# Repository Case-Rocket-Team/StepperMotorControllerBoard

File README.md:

"# StepperDriver" 
"# StepperMotorControllerBoard"

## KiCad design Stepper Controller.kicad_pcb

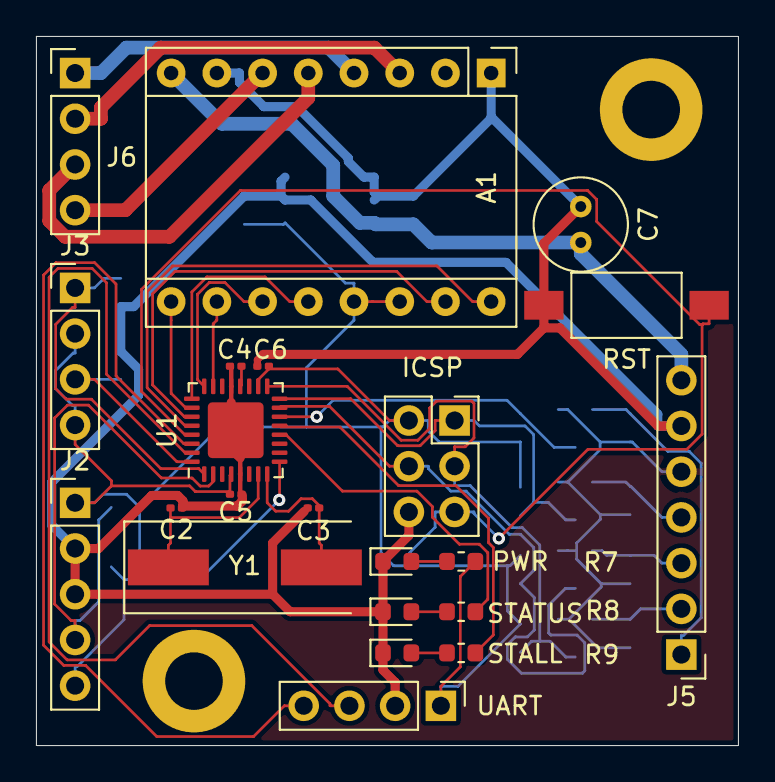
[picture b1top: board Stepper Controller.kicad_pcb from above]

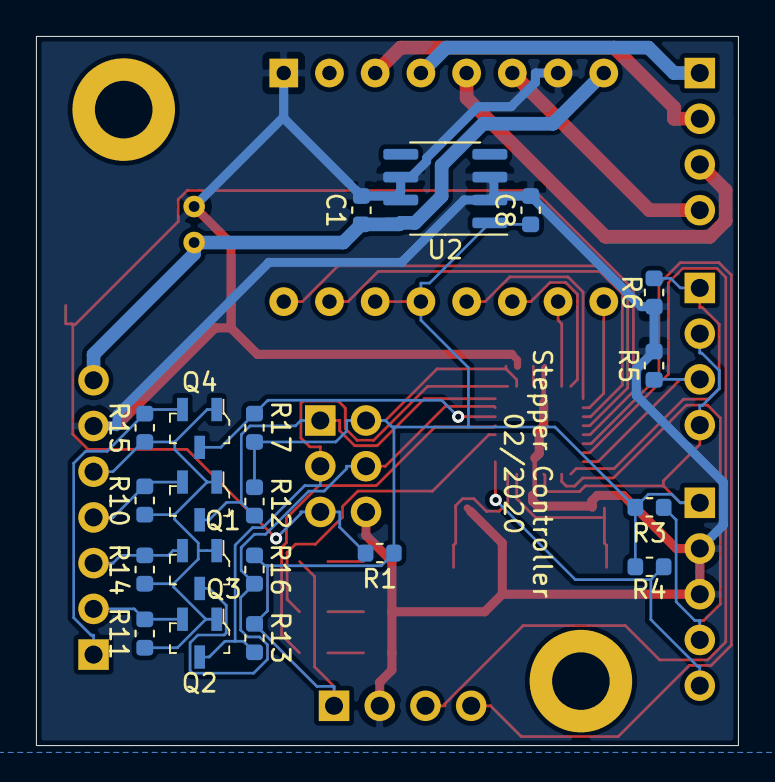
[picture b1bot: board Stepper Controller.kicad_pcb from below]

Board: 2 copper layers, 39.0 x 39.4 mm, 44 parts (20 on the bottom side), 37 nets.

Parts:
A1: Pololu_Breakout_DRV8825; Pololu_Breakout-16_15.2x20.3mm
C1: .33uF; C_0603_1608Metric
C2, C3: 22pf; C_0201_0603Metric
C4, C5, C6: 0.1uF; C_0201_0603Metric
C7: 100uf; C_Radial_D5.0mm_H5.0mm_P2.00mm
C8: .1uF; C_0603_1608Metric
J2: ENCODER; PinHeader_1x05_P2.54mm_Vertical
J3: LIMIT_SWITCH; PinHeader_1x04_P2.54mm_Vertical
J4: ICSP; PinSocket_2x03_P2.54mm_Vertical
J5: MAIN_CONNECTOR; PinHeader_1x07_P2.54mm_Vertical
J6: Stepper; PinHeader_1x04_P2.54mm_Vertical
PWR: PWR; LED_0603_1608Metric
Q1, Q2, Q3, Q4: BSS138; SOT-23-3
R1, R3, R4, R5, R6, R7, R8, R9, R10, R11, R12, R13, R14, R15, R16, R17: 10K; R_0603_1608Metric
REF1, REF2: MountingHole_3.2mm_M3_ISO7380_Pad
RST: RESET; SW_SPST_FSMSM
STALL: STALL; LED_0603_1608Metric
STATUS: STATUS; LED_0603_1608Metric
U1: ATmega328PB-MU; QFN-32-1EP_5x5mm_P0.5mm_EP3.1x3.1mm
U2: L78L05_SO8; SOIC-8_3.9x4.9mm_P1.27mm
UART: UART; PinHeader_1x04_P2.54mm_Vertical
Y1: 16 MHz; Crystal_SMD_HC49-SD

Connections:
+3V3: J5.5, Q1.1, Q2.1, Q3.1, Q4.1, R10.1, R11.1, R14.1, R15.1
+5V: A1.13, A1.14, C5.1, C6.1, C8.1, J2.1, J3.2, J3.4, J4.2, R1.1, R3.2, R4.2, R7.2, R12.1, R13.1, R16.1, R17.1, U1.4, U1.18, U2.1, UART.1
+12V: A1.8, C1.1, C7.2, J5.7, U2.8
CS_3V3: J5.1, Q4.2, R15.2
CS_5V: Q4.3, R17.2, U1.14
DIR: A1.16, U1.28
ENCDR_A: J2.4, R3.1, U1.2
ENCDR_B: J2.5, R4.1, U1.9
GND: A1.1, A1.7, C1.2, C2.2, C3.2, C4.2, C5.2, C6.2, C7.1, C8.2, J2.2, J2.3, J4.6, J5.6, PWR.1, R5.2, R6.1, RST.1, STALL.1, STATUS.1, U1.5, U1.21, U1.33, U2.2, U2.3, U2.6, U2.7, UART.2
M0: A1.10, U1.23
M1: A1.11, U1.24
M2: A1.12, U1.25
MAX: J3.1, R6.2, U1.1
MIN: J3.3, R5.1, U1.32
MISO_3V3: J5.4, Q1.2, R10.2
MISO_5V: J4.1, Q1.3, R12.2, U1.16
MOSI_3V3: J5.3, Q3.2, R14.2
MOSI_5V: J4.4, Q3.3, R16.2, U1.15
MOTOR_EN: A1.9, U1.26
unnamed: A1.3, J6.2
unnamed: A1.4, J6.1
unnamed: A1.5, J6.3
unnamed: A1.6, J6.4
unnamed: C4.1, U1.20
unnamed: PWR.2, R7.1
unnamed: R8.1, STATUS.2
unnamed: R9.1, STALL.2
RESET: J4.5, R1.2, RST.2, U1.29
RxD: U1.30, UART.4
SCK_3V3: J5.2, Q2.2, R11.2
SCK_5V: J4.3, Q2.3, R13.2, U1.17
STALL: R9.2, U1.13
STATUS: R8.2, U1.12
STEP: A1.15, U1.27
TxD: U1.31, UART.3
XTAL_1: C2.1, U1.7, Y1.1
XTAL_2: C3.1, U1.8, Y1.2

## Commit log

2020-01-27 Schematic Done
2020-09-22 completed
